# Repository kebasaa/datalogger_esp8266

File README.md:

# Asynchronous datalogger using ESP8266

Asynchronous datalogger using ESP8266 for logging scientific sensors to MicroSD

## Offline dashboard

The firmware starts a protected setup access point when it has no saved Wi-Fi
credentials and, after a 30-second station outage, exposes the dashboard again
through that access point. Change `HOTSPOT_PASSWORD`, `DASHBOARD_USER` and
`DASHBOARD_PASSWORD` in `src/main.cpp` before deployment.

Open `http://192.168.4.1/` on the access point, or the logger's address on your
network. The dashboard has four tabs:

- **Status** — whether the logger is actually recording, GPS fix and time
  quality, battery, free heap, MicroSD space and write errors, per-bus I2C
  health and the supervisor counters. Updates once a second.
- **Calibration** — sessions, live raw versus calibrated readings, zero/span
  and differential calibration, and the stored coefficients.
- **WiFi** — scan for networks and join one.
- **Console** — runs the same commands as the serial port, for when something
  needs poking at and no cable is to hand.

It is a small single-page app served from the logger's own flash: no internet
connection is needed and nothing is loaded from a CDN. It scales from a phone
in the field to a desktop browser, and follows your system's light or dark
theme (with a toggle to override).

> The web interface lives in `web/src/`. A pre-build script minifies and gzips
> it into `data/h4/`, so after changing it you must upload the filesystem as
> well as the firmware:
>
> ```bash
> pio run -e d1_mini_pro -t upload -t uploadfs
> ```

GPS is connected directly to the I2C bus. Its reader is deliberately separate
from the TCA9548A channels; do not pass the multiplexer to the GPS constructor
unless the hardware wiring changes.

Sensor & logger testing in the field

## Serial commands

The web interface has no private channel to the firmware: every button on it
runs one of the commands below, over `GET /rest/<command>/<parameters>`. So
anything the dashboard can do can also be done from the serial port or with
`curl`, which is what you want when no Wi-Fi is available, when calibrating
from a script, or when a logger needs rescuing.

### Connecting

Connect at **115200 baud** (`monitor_speed` in `platformio.ini`; the firmware
takes the same value through `PROJ_BAUD_RATE`):

```bash
pio device monitor -e d1_mini_pro
```

Type a command and press Enter. Parameters are separated by a forward slash,
with no spaces:

```
command/parameter/parameter/...
```

Commands are case-sensitive. `help` lists every command the firmware knows,
including the built-in H4 ones described at the end of this section.

### Overview

| Command | Parameters | Needs a session | What it does |
| --- | --- | --- | --- |
| `cal_start` | none | – | Starts a calibration session |
| `cal_stop` | none | yes | Saves everything measured in the session |
| `cal_discard` | none | yes | Throws the session away without saving |
| `cal` | 3–4 | yes | Measures the sensor and calibrates from the reading |
| `set` | 5 | yes | Stores a reference and a measured value entered by hand |
| `show_cal` | none | no | Prints all stored calibration values |
| `cal_reset` | none | no | Clears every stored coefficient (opens and closes its own session) |
| `cal_select` | 2–3 | no | Chooses which quantity and sensor the dashboard's live reading follows |

### Calibration sessions

Calibration values live in flash memory, which wears out if written to too
often. Rather than saving on every calibration, the firmware collects them in a
session and writes them once:

1. `cal_start` — begins recording. Values change in memory only.
2. Any number of `cal` and `set` commands.
3. `cal_stop` — writes everything to flash in a single operation and appends one
   row to `calibration_<date>.csv` on the SD card. The row needs a valid GPS
   date; without a fix the values are still saved to flash, but the log line is
   skipped and `Error: No GPS fix` is printed.

`cal_discard` ends the session and throws the collected values away, leaving
what was previously stored untouched. `cal` and `set` refuse to run outside a
session and answer `Can't do now`, so it is always clear when values reach
flash.

A session that is left open and untouched saves itself after the number of
minutes set by `CALIBRATION_TIMEOUT_MINUTES` in `src/main.cpp` (30 by default,
0 to disable), so a forgotten calibration is not lost. Values collected in an
open session are used immediately for the logged data and are visible to
`show_cal`, but a power cut before `cal_stop` loses them.

The session is shared with the dashboard, because they are the same thing: the
Calibration tab's buttons issue `cal_start`/`cal_stop`/`cal_discard`, so a
session begun over serial is visible in the browser and vice versa.

### Quantity names and units

The quantity is one of the names below. Which ones exist depends on the sensors
enabled in `src/main.cpp`:

| Name | Enabled by | Sensor measures | Reference for `cal/zero` | Reference for `cal/span` | Reference for `set` |
| --- | --- | --- | --- | --- | --- |
| `temperature` | `BME280_BUSES` | °C | °C | °C | °C |
| `pressure` | `BME280_BUSES` | Pa | Pa | Pa | Pa |
| `h2o` | `BME280_BUSES` | mmol/mol | mmol/mol | **dew point in °C** | mmol/mol |
| `co2` | `SCD30_BUSES` | ppm | ppm | ppm | ppm |
| `o2` | `SEN0465_BUSES` | % vol | % vol | % vol | % vol |

Water vapour is the one quantity whose reference is not always in the unit the
sensor reports, because the two calibration points are produced differently. A
span calibration uses a dew-point generator, so `cal/span/h2o/...` takes a **dew
point in °C** and converts it to a mole fraction using the measured air pressure.
A zero calibration uses dry gas, so `cal/zero/h2o/...` takes a mole fraction in
mmol/mol — `cal/zero/h2o/0` with no reference therefore calibrates against dry
air (0 mmol/mol), which is what flushing the sensor with a desiccant or zero air
gives you. `set` never converts anything, so it always expects mmol/mol.

The same split applies to the dashboard: for water vapour the "Zero gas" box is
in mmol/mol and the "Span gas" box is a dew point in °C.

Sensor numbers are **0-based**: with `BME280_BUSES 0, 1` the two sensors are
`0` and `1`. For `cal/zero` and `cal/span`, a sensor number that does not exist
is skipped rather than stored.

### `cal` — measure and calibrate

Takes a reading from the sensor itself and stores it against a known reference.
It averages 10 readings taken about one second apart, so it takes roughly ten
seconds; the command returns immediately and the result appears afterwards.

```
cal/zero/<quantity>/<sensor>
cal/zero/<quantity>/<sensor>/<reference>
cal/span/<quantity>/<sensor>/<reference>
cal/diff/<quantity>/low
cal/diff/<quantity>/high
```

`zero` without a reference uses 0.0. `span` always needs one.

```
cal/zero/co2/1              zero-calibrate CO2 sensor 1 against 0 ppm
cal/zero/co2/1/0.54         zero-calibrate CO2 sensor 1 against 0.54 ppm
cal/span/co2/1/409.87       span-calibrate CO2 sensor 1 against 409.87 ppm
cal/zero/h2o/0              zero-calibrate H2O sensor 0 against dry air (0 mmol/mol)
cal/zero/h2o/0/0.05         zero-calibrate H2O sensor 0 against 0.05 mmol/mol
cal/span/h2o/0/1.31         span-calibrate H2O sensor 0 against a 1.31 °C dew point
cal/span/temperature/0/20.5 span-calibrate temperature sensor 0 against 20.5 °C
cal/diff/co2/low            measure both CO2 sensors at the low concentration
cal/diff/co2/high           measure both CO2 sensors at the high concentration
```

Timing rules the firmware enforces:

- A `span` calibration must follow its `zero` by at least 10 seconds and no more
  than 2 hours, otherwise it is rejected and the reason is printed. Temperature
  is exempt from the 2-hour limit.
- `cal/diff/<quantity>/high` must follow the matching `low` by 10 to 600
  seconds. After 600 seconds only a simple offset is applied instead of a full
  linear correction, and the firmware says so.
- `cal/diff` measures sensors 0 and 1 together and so needs two sensors of that
  type. It takes no sensor number.
- Only one calibration runs at a time; a second one while the first is still
  measuring is ignored.

### `set` — enter values by hand

Stores a reference value and the corresponding sensor reading without measuring
anything. Useful for entering figures from a calibration certificate or from an
earlier session. Requires exactly five parameters.

```
set/<zero|span>/<quantity>/<sensor>/<reference>/<measured>
```

```
set/zero/co2/1/12.07/13.08      sensor 1 read 13.08 ppm when the true value was 12.07
set/span/co2/1/376.87/402.87    sensor 1 read 402.87 ppm when the true value was 376.87
```

Unlike `cal`, `set` ignores the timing rules above, so a `span` can be entered
without a preceding `zero`.

### `show_cal`

Prints every stored calibration value, including values collected in a session
that has not been saved yet. Works with or without a session.

```
show_cal
```

```
Calibration coefficients:
  - sen_co2_0_zero: 13.08
  - sen_co2_0_span: 402.87
  - sen_co2_0_diff: nan
  ...
```

The names read `<sen|ref>_<quantity>_<sensor>_<type>`, where `ref_` is the known
reference value and `sen_` is what the sensor read. For the `diff` type, `ref_`
holds the low value and `sen_` the high one. `nan` means not calibrated.

### `cal_reset`

Clears every stored calibration coefficient, for every quantity and sensor.
This is the "Reset all" button on the Calibration tab. It does not need a
session: if none is open it opens and closes one itself, so the whole reset
costs a single write to flash.

```
cal_reset
```

### `cal_select`

Chooses which quantity and sensor the dashboard's live reading follows. It
changes nothing that gets logged and no calibration depends on it — `cal` and
`set` always take their quantity and sensor as explicit parameters.

```
cal_select/<quantity>/<sensor>[/<differential quantity>]
```

```
cal_select/co2/1
cal_select/co2/1/h2o
```

Until a selection is made the logger does not read a sensor for the dashboard
at all, which keeps the web interface off the I2C bus unless someone is
actually watching a value.

### Worked examples

A full zero and span calibration of one CO<sub>2</sub> sensor, saved in a single
write to flash:

```
cal_start
cal/zero/co2/1                 (flush with zero gas, wait ~10 s for the reading)
cal/span/co2/1/409.87          (flush with 409.87 ppm span gas, at least 10 s later)
show_cal                       (check the values before committing to them)
cal_stop
```

A differential calibration comparing two sensors, where the second run went
wrong and is thrown away:

```
cal_start
cal/diff/co2/low               (both sensors at the low concentration)
cal/diff/co2/high              (both sensors at the high concentration, 10-600 s later)
cal_discard                    (nothing is written; the old values remain)
```

Entering values from a certificate for both sensors:

```
cal_start
set/zero/co2/0/0.0/1.42
set/span/co2/0/400.0/398.15
set/zero/co2/1/0.0/2.07
set/span/co2/1/400.0/403.44
cal_stop
```

### Replies

A command that succeeds prints its own progress messages and nothing else. A
command that fails prints one of these, in addition to a line explaining what
was wrong:

| Reply | Meaning |
| --- | --- |
| `Unknown cmd` | No such command |
| `Too few parameters` | Not enough parameters |
| `Too many parameters` | Too many parameters |
| `Numeric value expected` | A sensor number or reference value was not a number |
| `Incorrect Payload Format` | An unknown quantity, calibration type, or something other than `low`/`high` |
| `Can't do now` | No session open, or a session is already open |

Calibrations rejected by the timing rules are reported as plain text, for
example `<10s since zero calibration. Are you sure the span gas is stable?`.

### Built-in commands

H4, the framework underneath, adds its own commands. Run `help` for the full
list, which depends on how the framework is configured — the reporting commands
(`h4/show/...`) are compiled out in this build, because `H4P_LOG_MESSAGES` is 0.
The ones worth knowing:

| Command | What it does |
| --- | --- |
| `help` | Lists every available command |
| `h4/reboot` | Restarts the logger |
| `h4/clear` | Erases all stored settings, **including every calibration** |
| `h4/factory` | Factory reset; also erases every calibration |

Both `h4/clear` and `h4/factory` delete the file the calibrations live in. Save
anything you need first — `show_cal` prints the values, and every `cal_stop`
appends them to `calibration_<date>.csv` on the SD card.

`h4/factory` is also the way back into access-point mode: it clears the stored
Wi-Fi credentials, so the logger starts its own hotspot on the next boot.
Follow it with `h4/reboot`.

### Over HTTP

Every command above is also reachable at `GET /rest/<command>/<parameters>`,
protected by the same login as the dashboard:

```bash
curl -u admin:datalogger http://<logger-address>/rest/show_cal
curl -u admin:datalogger http://<logger-address>/rest/cal/zero/co2/1
```

The reply is JSON — `res` is 0 on success, and `lines` holds what the command
printed:

```json
{"res":0,"msg":"OK","lines":["Calibration coefficients:","  - sen_co2_0_zero: 13.08"]}
```

Alongside the commands there are a few read-only endpoints the dashboard uses,
which are also handy for scripted monitoring:

| Endpoint | What it returns |
| --- | --- |
| `GET /api/status` | One JSON snapshot of everything on the Status tab |
| `GET /api/events` | The same payload once a second, as a server-sent event stream |
| `GET /api/cal` | Stored calibration coefficients, as JSON |
| `GET /api/wifi/scan` | Networks the logger can see (access-point mode only) |

## Prerequisites
- Requires a GPS module for date, time and location

The following sensors/components are implemented currently:
- [Texas Instruments ADS1115](https://www.ti.com/product/ADS1115) analogue multiplexer
- [Texas Instruments TCA9548](https://www.ti.com/product/TCA9548A) i<sup>2</sup>c multiplexer
- MicroSD card data storage with circular storage buffer
- Analogue battery charge reading (voltage)
- Environmental physics equations
- [Sierra Wireless XA1110](https://source.sierrawireless.com/devices/positioning-modules/xa1110/) GPS module
- [Sensirion SCD-30](https://sensirion.com/products/catalog/SCD30) CO<sub>2</sub> sensor
- [DFRobot SEN0465](https://www.dfrobot.com/product-2510.html) O<sub>2</sub> sensor
- [Bosch BME280](https://www.bosch-sensortec.com/products/environmental-sensors/humidity-sensors-bme280/) air temperature, relative humidity & pressure sensor
- [Melexis MLX90614](https://www.melexis.com/en/product/MLX90614/Digital-Plug-Play-Infrared-Thermometer-TO-Can) thermal radiation sensor
- WIFI & web interface
- Zero, span and differential calibration of every measured quantity, controlled
  from the web interface or the serial port (see [Serial commands](#serial-commands)),
  collected into sessions so a calibration is written to flash only once

To be done:
- Single-bus operation (`I2C_MULTI 0` in `src/config.h`) does not currently
  compile; only the multiplexed dual-bus configuration builds
- When the dashboard pre-fills the "Span gas" box for water vapour it shows the
  stored mole fraction, although the box expects a dew point. Displaying it as a
  dew point needs a mole-fraction-to-dew-point conversion, which
  `lib/Environmental` does not have yet
- Guard the differential-to-absolute conversion against division by zero when
  the two differential calibration points are nearly equal
- The differential check that rejects a high calibration point too close to the
  low one uses a fixed threshold of 100, regardless of the unit of the quantity
  being calibrated
- Cache the calibration coefficients instead of re-reading twelve stored values
  on every conversion, once per second per quantity

## How to Cite

This citation does not work yet. Simply cite the github repository as a website for now:
Muller (2025). *datalogger_esp8266: Asynchronous datalogger using ESP8266*

## License

This software is distributed under the GNU GPL version 3. Any modification of the code in this repository may only be released under the same license, and with attribution of authorship of the original code (i.e., citation above).

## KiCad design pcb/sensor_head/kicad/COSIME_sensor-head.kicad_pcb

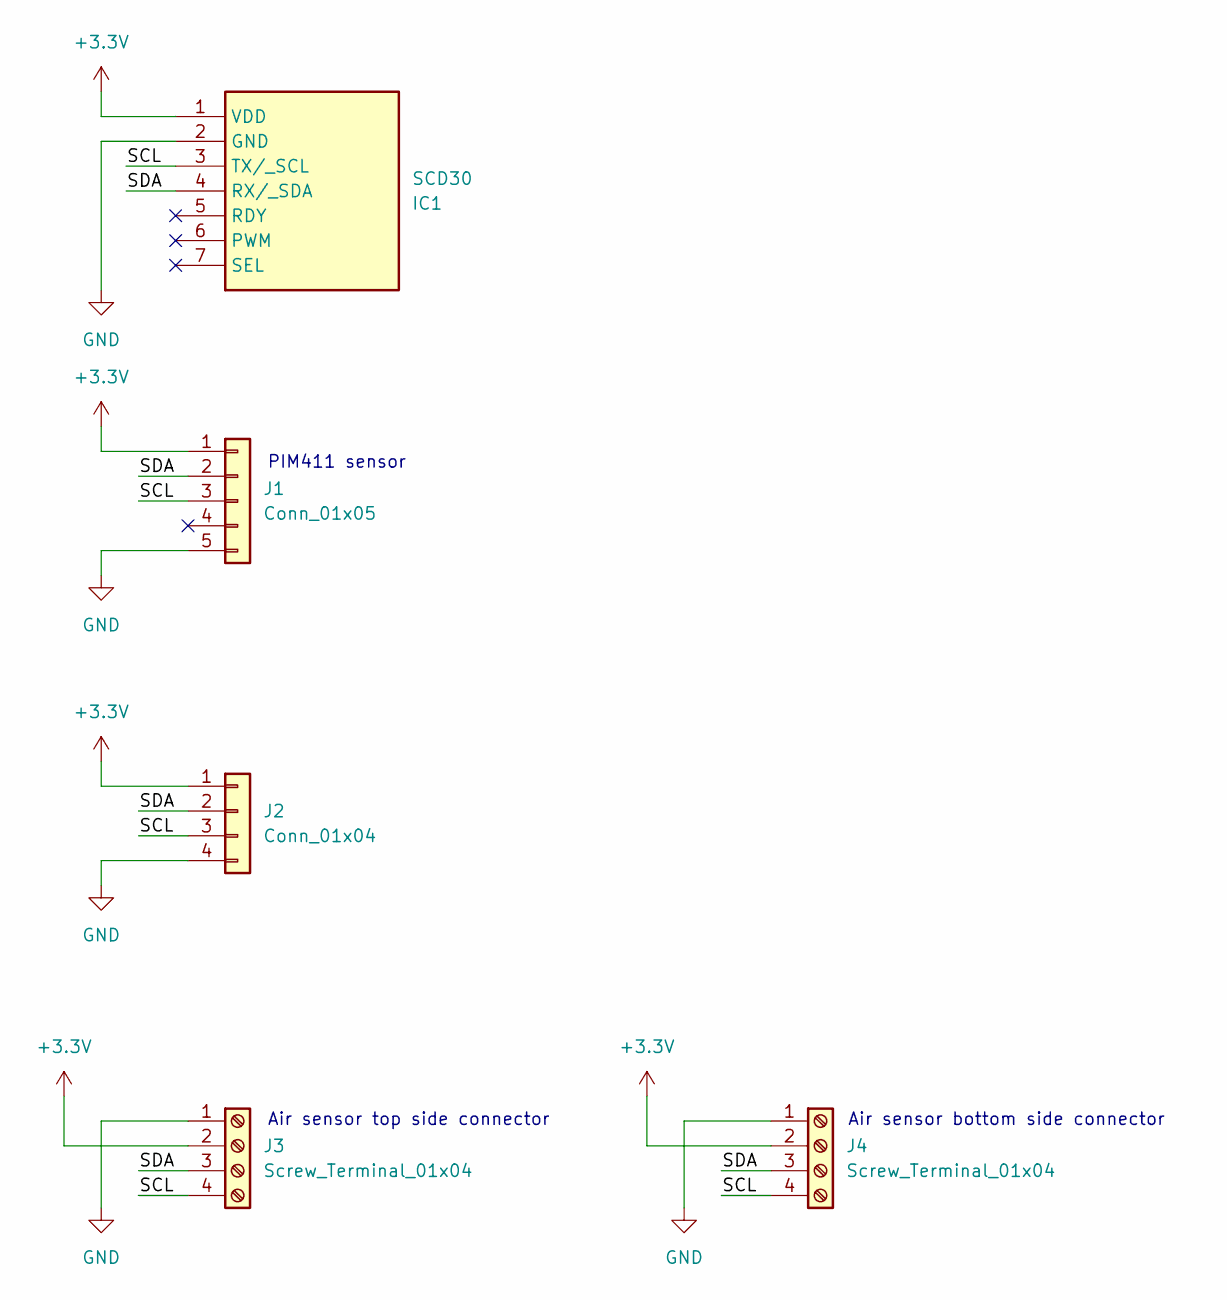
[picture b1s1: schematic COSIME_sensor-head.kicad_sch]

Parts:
IC1: SCD30; Manufacturer_Part_Number SCD30; Mouser Part Number 403-SCD30
J1: Conn_01x05; PinSocket_1x05_P2.54mm_Vertical
J2: Conn_01x04; PinSocket_1x04_P2.54mm_Vertical
J3, J4: Screw_Terminal_01x04; 1778719

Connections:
+3.3V: IC1.1 (VDD), J1.1, J2.1, J3.2, J4.2
/SCL: IC1.3 (TX/_SCL), J1.3, J2.3, J3.4, J4.4
/SDA: IC1.4 (RX/_SDA), J1.2, J2.2, J3.3, J4.3
GND: IC1.2 (GND), J1.5, J2.4, J3.1, J4.1

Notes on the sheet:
Air sensor top side connector
Air sensor bottom side connector
PIM411 sensor

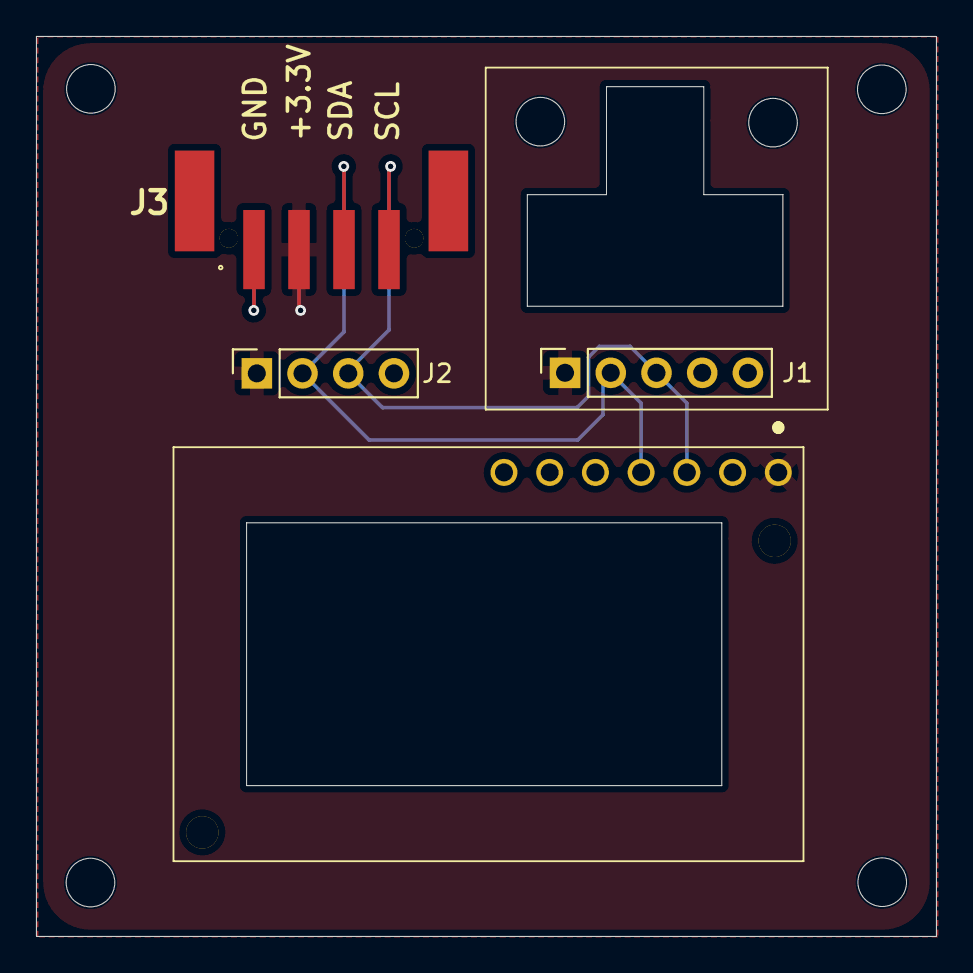
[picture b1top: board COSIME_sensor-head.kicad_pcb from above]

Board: 2 copper layers, 50.0 x 50.0 mm, 5 parts (1 on the bottom side), 4 nets.

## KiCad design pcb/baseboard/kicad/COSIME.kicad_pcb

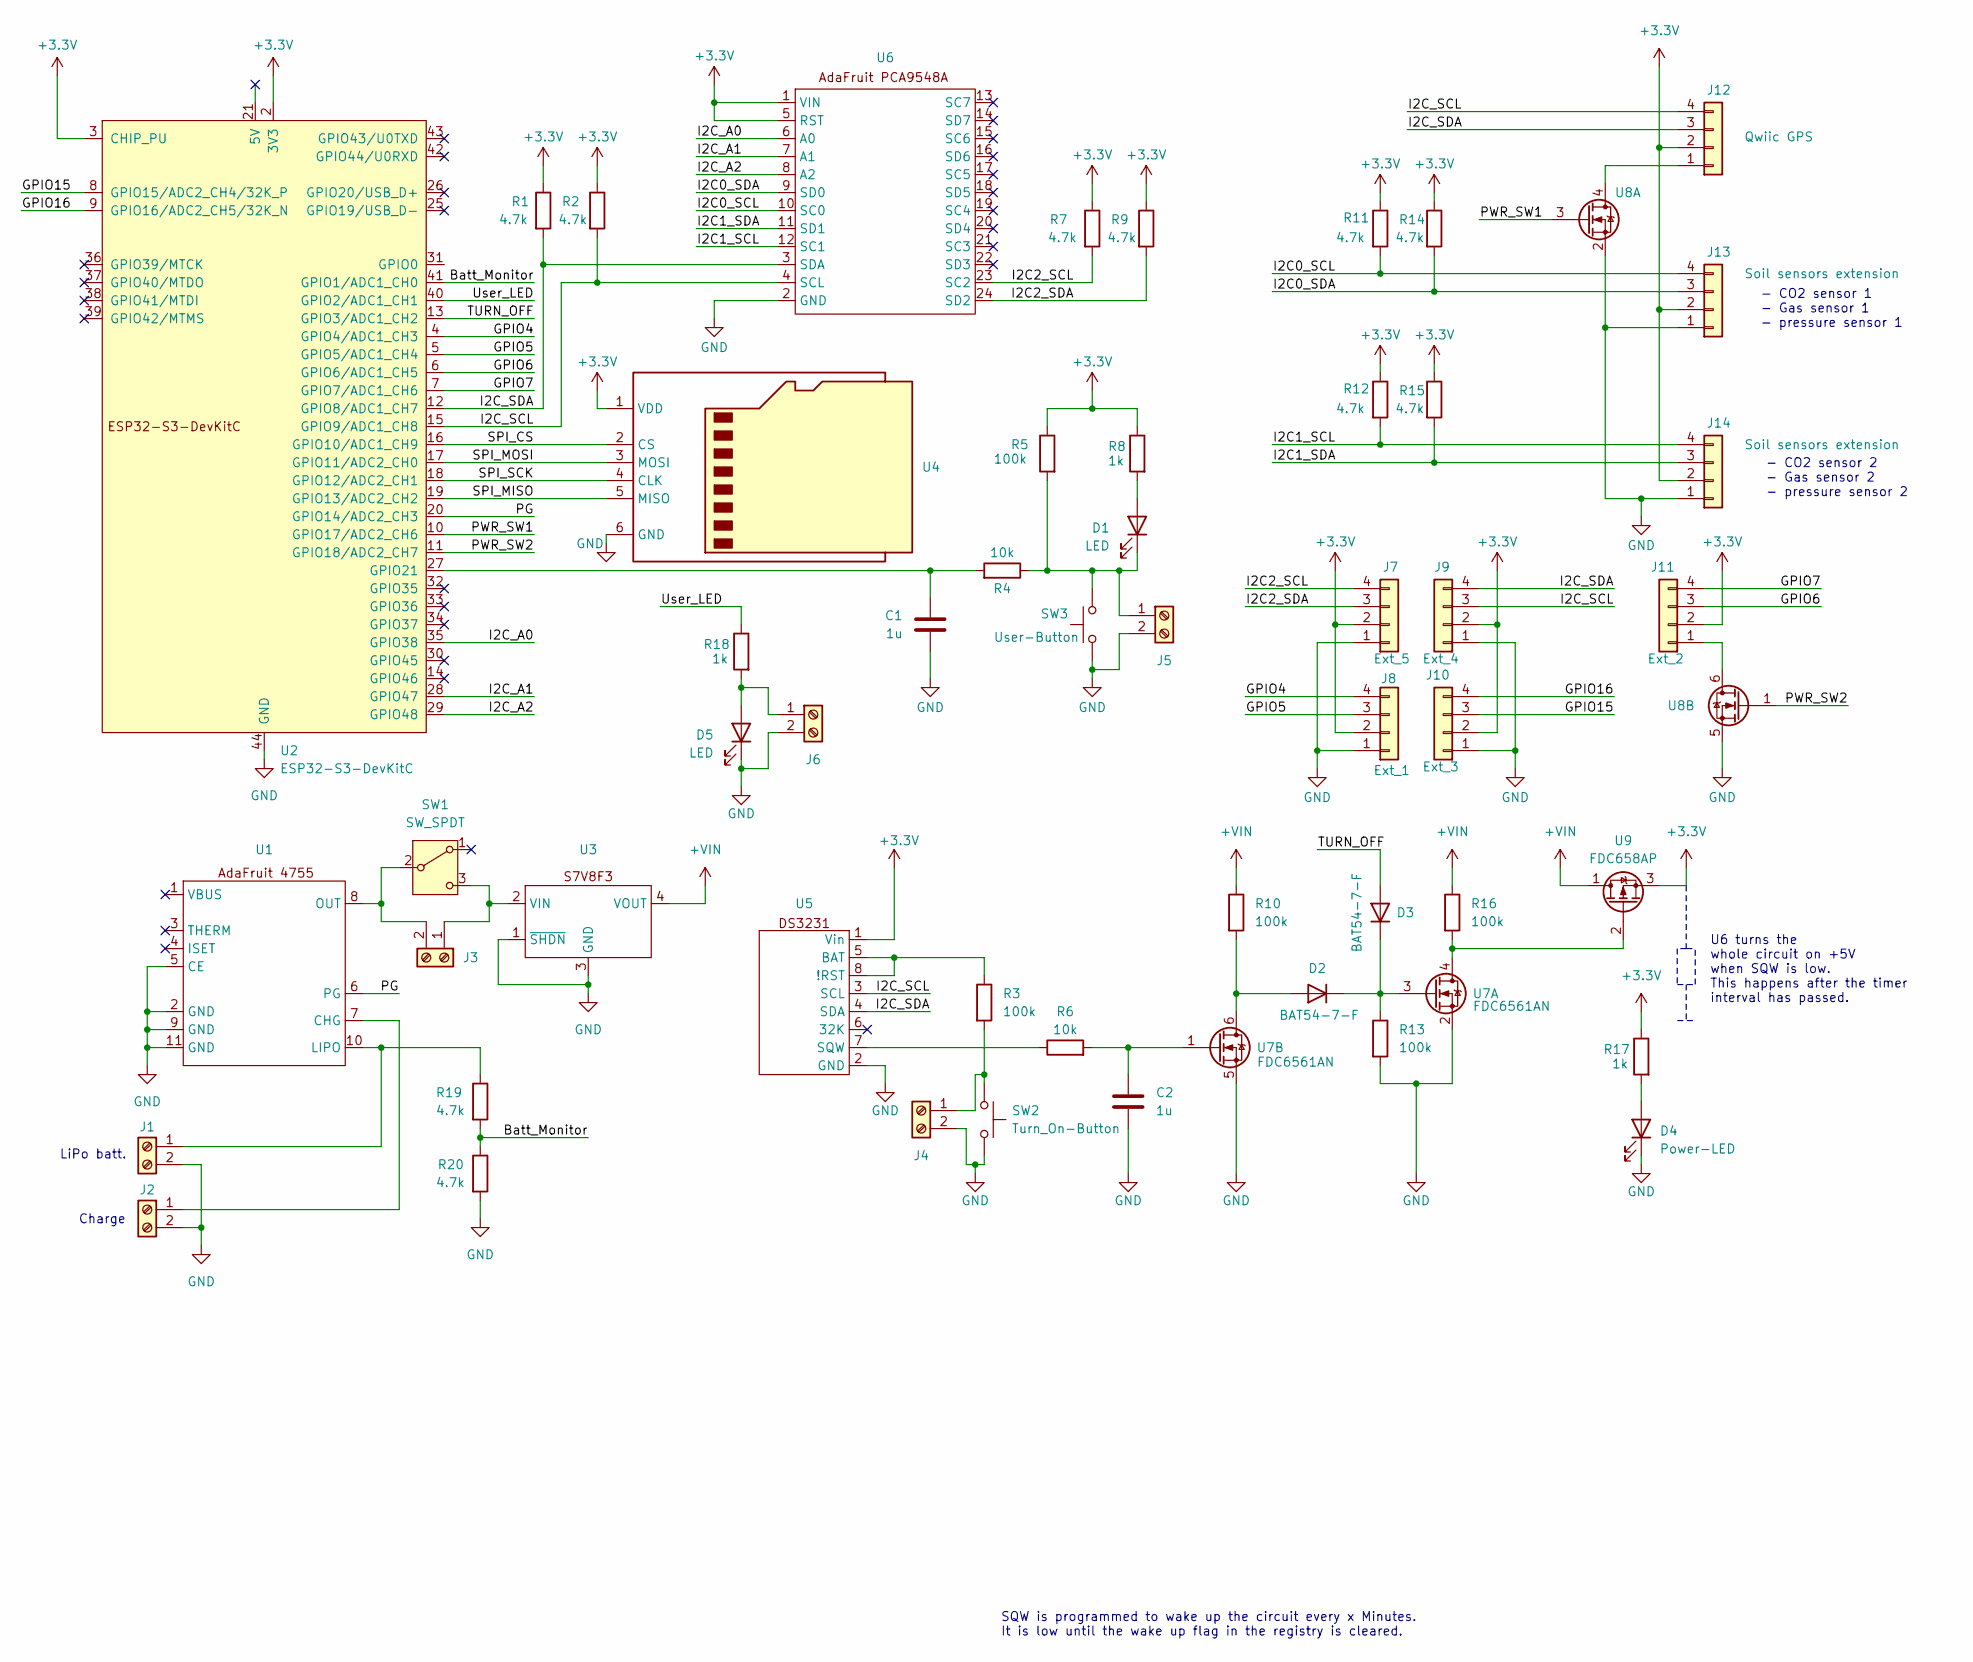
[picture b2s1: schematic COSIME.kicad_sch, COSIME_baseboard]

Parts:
C1, C2: 1u; C_0603_1608Metric_Pad1.08x0.95mm_HandSolder
D1, D5: LED; LED_0805_2012Metric_Pad1.15x1.40mm_HandSolder
D2, D3: BAT54-7-F; D_DO-35_SOD27_P7.62mm_Horizontal
D4: Power-LED; LED_0805_2012Metric_Pad1.15x1.40mm_HandSolder
J1, J2, J3, J4, J5, J6: Screw_Terminal_01x02; 1839198
J7: Ext_5; 1778719
J8: Ext_1; 1778719
J9: Ext_4; 1778719
J10: Ext_3; 1778719
J11: Ext_2; 1778719
J12: Qwiic GPS; 1778719
J13, J14: Soil sensors extension; 1778719
R1, R2, R7, R9, R11, R12, R14, R15, R19, R20: 4.7k; R_0603_1608Metric_Pad0.98x0.95mm_HandSolder
R3, R5, R10, R13, R16: 100k; R_0603_1608Metric_Pad0.98x0.95mm_HandSolder
R4, R6: 10k; R_0603_1608Metric_Pad0.98x0.95mm_HandSolder
R8, R17, R18: 1k; R_0603_1608Metric_Pad0.98x0.95mm_HandSolder
SW1: SW_SPDT; 500SSP1S2M2QEA
SW2: Turn_On-Button; SW_SPST_TL3305A
SW3: User-Button; SW_SPST_TL3305A
U1: 4755
U2: ESP32-S3-DevKitC
U3: Pololu_S7V8X
U4: MSD_BO1_SD-Card_Reader
U5: DS3231_Adafruit
U6: TCA9548A_AdaFruit
U7: FDC6561AN; SOT95P280X110-6N
U8: SOT95P280X110-6N
U9: FDC658AP; SOT95P275X110-6N_FDC658AP; Manufacturer_Part_Number FDC658AP; Mouser Part Number 512-FDC658AP

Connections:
+3.3V: J7.2, J8.2, J9.2, J10.2, J11.2, J12.2, J13.2, J14.2, R1.1, R2.1, R5.1, R7.1, R8.1, R9.1, R11.1, R12.1, R14.1, R15.1, R17.1, U2.1 (3V3), U2.2 (3V3), U2.3 (CHIP_PU), U4.1 (VDD), U5.1 (Vin), U6.1 (VIN), U6.5 (RST), U9.3
+VIN: R10.1, R16.1, U3.4 (VOUT), U9.1
/<NO NET>: J9.3, J12.4, R2.2, U2.15 (GPIO9/ADC1_CH8), U5.3 (SCL), U6.4 (SCL)
/Batt_Monitor: R19.2, R20.1, U2.41 (GPIO1/ADC1_CH0)
/GPIO4: J8.4, U2.4 (GPIO4/ADC1_CH3)
/GPIO5: J8.3, U2.5 (GPIO5/ADC1_CH4)
/GPIO6: J11.3, U2.6 (GPIO6/ADC1_CH5)
/GPIO7: J11.4, U2.7 (GPIO7/ADC1_CH6)
/GPIO15: J10.3, U2.8 (GPIO15/ADC2_CH4/32K_P)
/GPIO16: J10.4, U2.9 (GPIO16/ADC2_CH5/32K_N)
/I2C0_SCL: J13.4, R11.2, U6.10 (SC0)
/I2C0_SDA: J13.3, R14.2, U6.9 (SD0)
/I2C1_SCL: J14.4, R12.2, U6.12 (SC1)
/I2C1_SDA: J14.3, R15.2, U6.11 (SD1)
/I2C2_SCL: J7.4, R7.2, U6.23 (SC2)
/I2C2_SDA: J7.3, R9.2, U6.24 (SD2)
/I2C_A0: U2.35 (GPIO38), U6.6 (A0)
/I2C_A1: U2.28 (GPIO47), U6.7 (A1)
/I2C_A2: U2.29 (GPIO48), U6.8 (A2)
/I2C_SDA: J9.4, J12.3, R1.2, U2.12 (GPIO8/ADC1_CH7), U5.4 (SDA), U6.3 (SDA)
/PG: U1.6 (PG), U2.20 (GPIO14/ADC2_CH3)
/PWR_SW1: U2.10 (GPIO17/ADC2_CH6), U8.3
/PWR_SW2: U2.11 (GPIO18/ADC2_CH7), U8.1
/SPI_CS: U2.16 (GPIO10/ADC1_CH9), U4.2 (CS)
/SPI_MISO: U2.19 (GPIO13/ADC2_CH2), U4.5 (MISO)
/SPI_MOSI: U2.17 (GPIO11/ADC2_CH0), U4.3 (MOSI)
/SPI_SCK: U2.18 (GPIO12/ADC2_CH1), U4.4 (CLK)
/TURN_OFF: D3.2 (A), U2.13 (GPIO3/ADC1_CH2)
/User_LED: R18.1, U2.40 (GPIO2/ADC1_CH1)
GND: C1.2, C2.2, D4.1 (K), D5.1 (K), J1.2, J2.2, J4.2, J5.2, J6.2, J7.1, J8.1, J9.1, J10.1, J13.1, J14.1, R13.2, R20.2, SW2.2, SW3.2, U1.2 (GND), U1.5 (CE), U1.9 (GND), U1.11 (GND), U2.22 (GND), U2.23 (GND), U2.24 (GND), U2.44 (GND), U3.1 (~SHDN), U3.3 (GND), U4.6 (GND), U5.2 (GND), U6.2 (GND), U7.2, U7.5, U8.2, U8.5
unnamed: C2.1, R6.2, U7.1
unnamed: D1.2 (A), R8.2
unnamed: D1.1 (K), J5.1, R4.1, R5.2, SW3.1
unnamed: D2.2 (A), R10.2, U7.6
unnamed: D2.1 (K), D3.1 (K), R13.1, U7.3
unnamed: D4.2 (A), R17.2
unnamed: D5.2 (A), J6.1, R18.2
unnamed: J1.1, R19.1, U1.10 (LIPO)
unnamed: J2.1, U1.7 (CHG)
unnamed: J3.1, SW1.3 (C), U3.2 (VIN)
unnamed: J3.2, SW1.2 (B), U1.8 (OUT)
unnamed: J4.1, R3.2, SW2.1
unnamed: J11.1, U8.6
unnamed: J12.1, U8.4
unnamed: R16.2, U7.4, U9.2
unnamed: C1.1, R4.2, U2.27 (GPIO21)
unnamed: R3.1, U5.5 (BAT), U5.8 (!RST)
unnamed: R6.1, U5.7 (SQW)

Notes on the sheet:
U6 turns the whole circuit on +5V when SQW is low. This happens after the timer interval has passed.
SQW is programmed to wake up the circuit every x Minutes. It is low until the wake up flag in the registry is cleared.
LiPo batt.
Charge
- CO2 sensor 1 - Gas sensor 1 - pressure sensor 1
- CO2 sensor 2 - Gas sensor 2 - pressure sensor 2

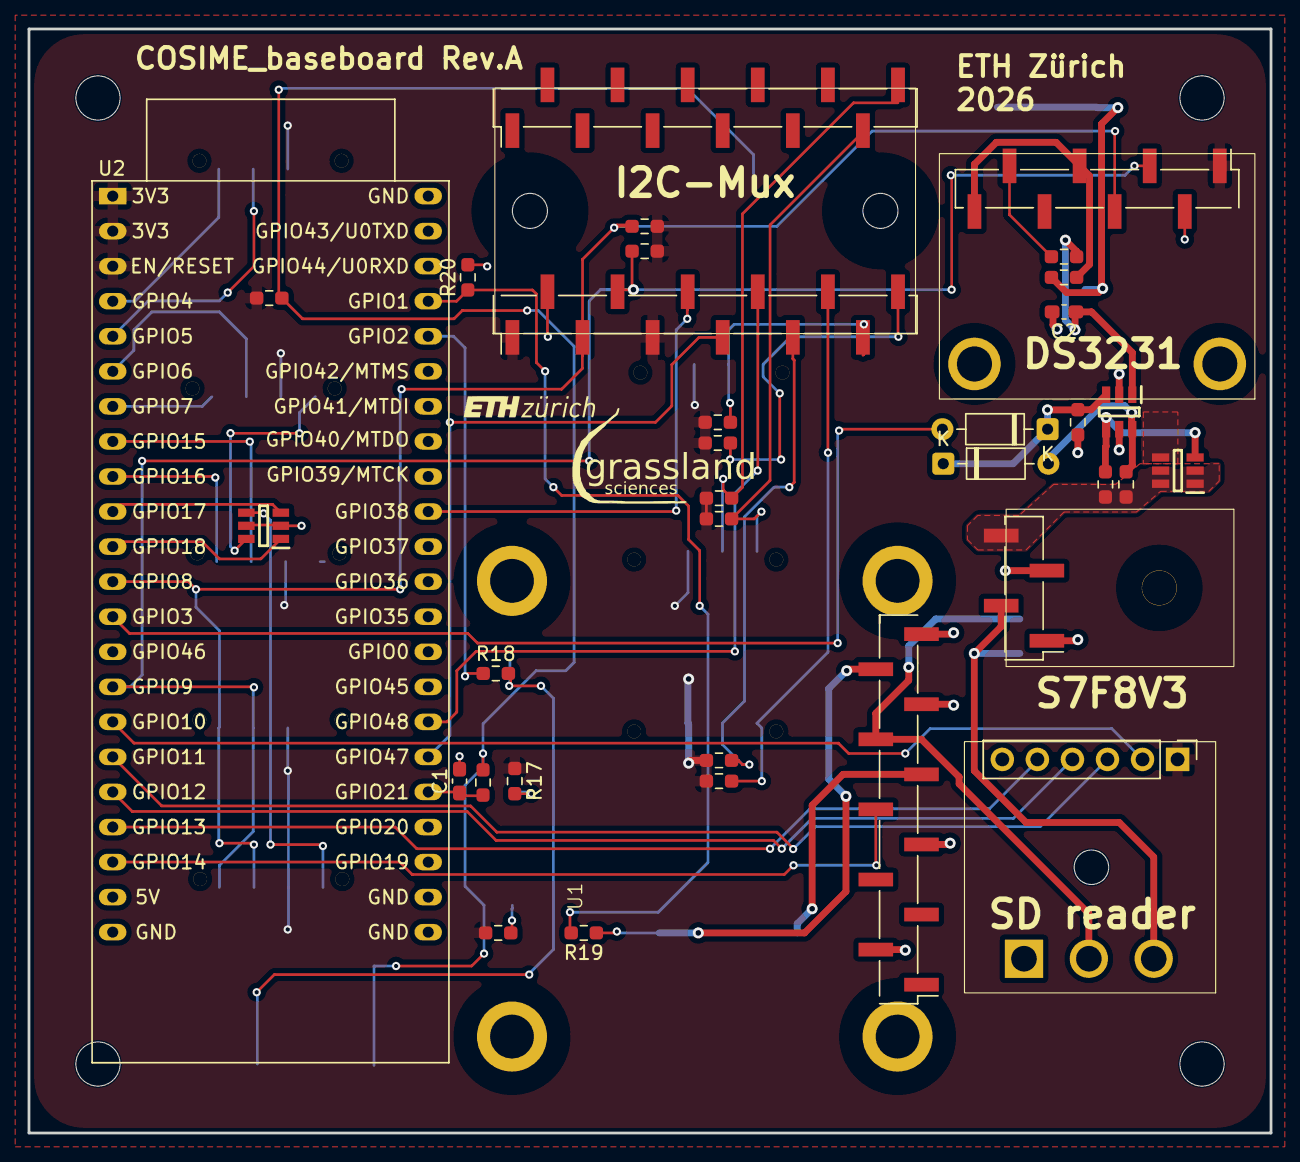
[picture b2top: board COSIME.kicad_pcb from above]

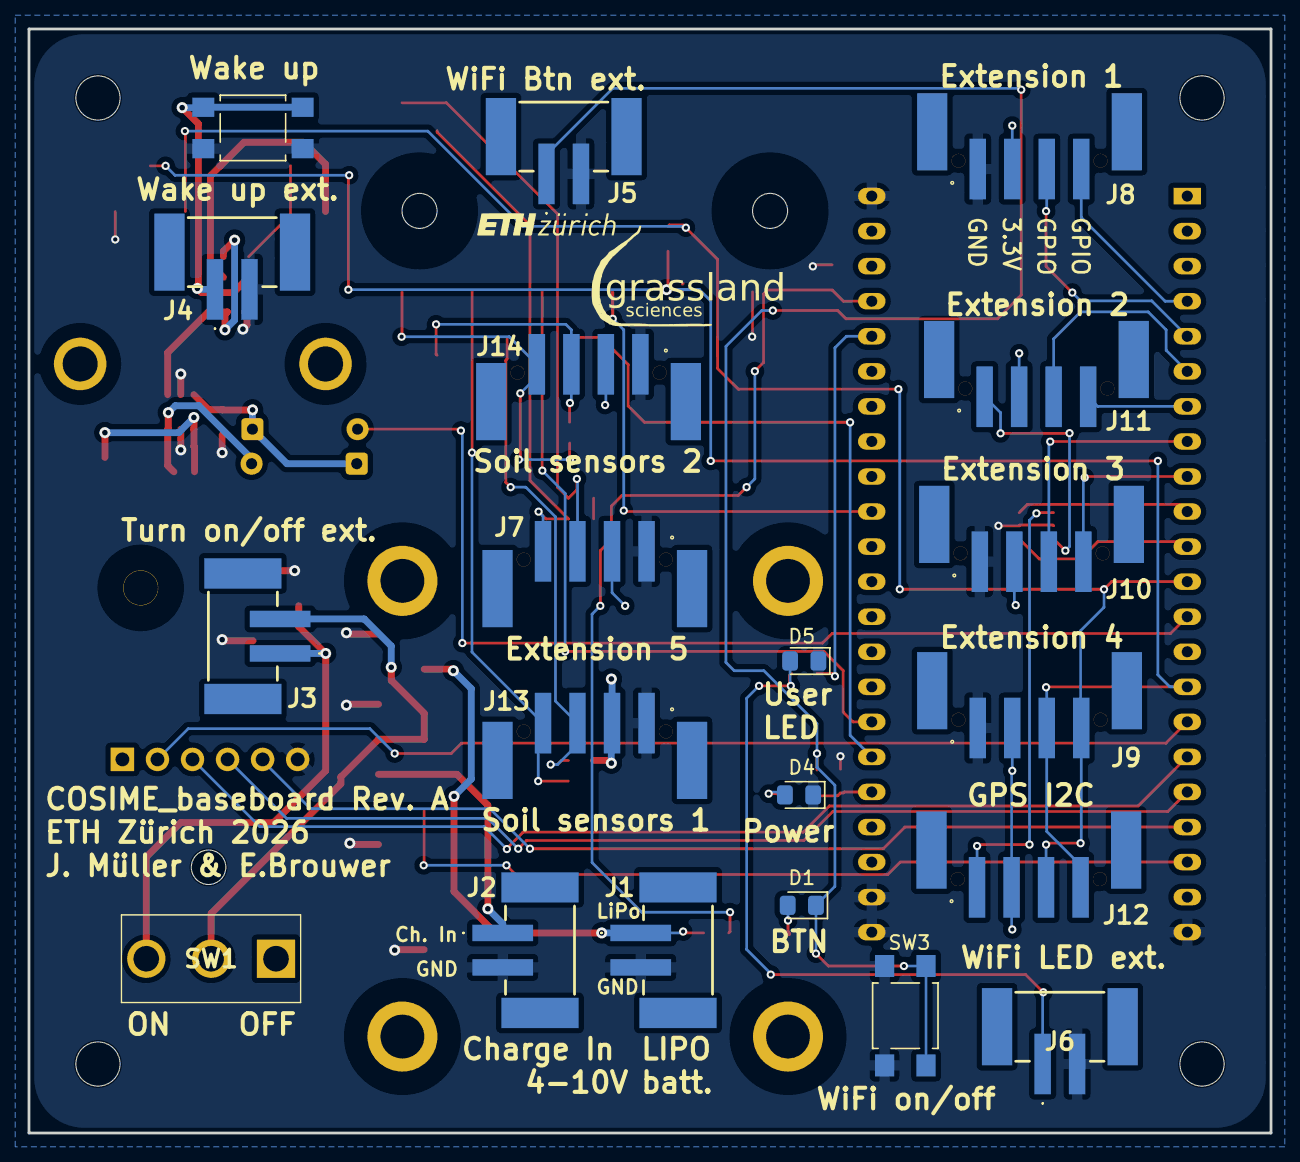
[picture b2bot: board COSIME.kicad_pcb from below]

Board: 2 copper layers, 90.0 x 80.0 mm, 53 parts (20 on the bottom side), 48 nets.

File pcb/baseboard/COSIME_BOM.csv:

Reference;Qty;Qty for 3;Value;stock;Footprint;Datasheet
C1,C2;2;6;1u;M;603;
D1,D5;2;6;LED;M;LED_SMD:LED_0805_2012Metric_Pad1.15x1.40mm_HandSolder;
D2,D3;2;6;BAT54-7-F;M;Diode_THT:D_DO-35_SOD27_P7.62mm_Horizontal;http://www.vishay.com/docs/85622/1n914.pdf
D4;1;3;Power-LED;M;LED_SMD:LED_0805_2012Metric_Pad1.15x1.40mm_HandSolder;
J1,J2,J3,J4,J5,J6;6;18;Screw_Terminal_01x02;M;SamacSys_Parts1:1839198;
J7;1;3;Ext_5;M;SamacSys_Parts1:1778719;
J8;1;3;Ext_1;M;SamacSys_Parts1:1778719;
J9;1;3;Ext_4;M;SamacSys_Parts1:1778719;
J10;1;3;Ext_3;M;SamacSys_Parts1:1778719;
J11;1;3;Ext_2;M;SamacSys_Parts1:1778719;
J12;1;3;Qwiic GPS;M;SamacSys_Parts1:1778719;
J13,J14;2;6;Soil sensors extension;M;SamacSys_Parts1:1778719;
R1,R2,R7,R9,R11,R12,R14,R15;8;24;4.7k;no;Resistor_SMD:R_0603_1608Metric_Pad0.98x0.95mm_HandSolder;
R3,R5,R10,R13,R16;5;15;100k;M;Resistor_SMD:R_0603_1608Metric_Pad0.98x0.95mm_HandSolder;
R4,R6;2;6;10k;M;Resistor_SMD:R_0603_1608Metric_Pad0.98x0.95mm_HandSolder;
R8,R17,R18;3;9;1k;M;Resistor_SMD:R_0603_1608Metric_Pad0.98x0.95mm_HandSolder;
SW1;1;3;SW_SPDT;M;SamacSys_Parts1:500SSP1S2M2QEA;
SW2;1;3;Turn_On-Button;M;Button_Switch_SMD:SW_SPST_TL3305A;
SW3;1;3;User-Button;M;Button_Switch_SMD:SW_SPST_TL3305A;
U1;1;3;;M;SamacSys_Parts1:4755;https://www.digikey.ch/de/products/detail/adafruit-industrie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
U2;1;3;ESP32-S3-DevKitC;M;PCM_Espressif:ESP32-S3-DevKitC;https://www.mouser.ch/de/ProductDetail/Espressif-Systems/ESP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
U3;1;3;;Eck;SamacSys_Parts1:Pololu_S7V8X;https://eckstein-shop.de/Pololu33VStep-UpStep-DownSpannungsr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
U4;1;3;;BB;SamacSys_Parts1:MSD_BO1_SD-Card_Reader;https://www.berrybase.de/en/micro-sd-card-reader-modul-mit-s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
U5;1;3;;M;SamacSys_Parts1:DS3231_Adafruit;https://www.bastelgarage.ch/rtc-ds3231-zeitmodul-mit-at24c32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
U6;1;3;;M;SamacSys_Parts1:TCA9548A_AdaFruit;https://www.bastelgarage.ch/8-kanal-i2c-multiplexer-tca9548asu
U7, U8;2;6;FDC6561AN;M;SamacSys_Parts1:SOT95P280X110-6N;
U9;1;3;FDC658AP;M;SamacSys_Parts1:SOT95P275X110-6N_FDC658AP;https://www.onsemi.com/pub/Collateral/FDC658AP-D.PDF
;2;6;PIM411 ;M;;https://www.mouser.ch/de/ProductDetail/Pimoroni/PIM411?qs=vL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
;2;6;SCD30;M;;
;1;3;CR1220;no;3V battery;

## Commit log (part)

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2025-06-19 Updated code & Readme
2025-06-28 Work on physics and sensors
    - Added environmental library (physics)
    - Remove SO-411 (non-functional)
    - Add testing routine for various tests
    - Minor changes to SD card, MLX90614 & GPS
    - Minor changes to BME280
2025-06-28 Remove obsolete stuff
2025-06-28 Minor changes
2025-06-28 Support for multiple i2c buses
2025-07-02 Implement O2 sensor
2025-07-02 Add O2 sensor and reorganise
2025-07-02 Update README & platformio requirements
2025-07-02 Add all sensors on both buses
2025-07-02 Rename battery library
2025-07-30 Update web/mobile interface
2025-08-27 Update buttons
2025-09-03 Smaller img for faster loading
2025-09-04 Update comment
2025-09-04 Minor fixes
2025-09-04 Add preliminary calibration logic
2025-09-08 Added calibration logic
2025-09-08 Update calibration logic
2025-09-23 Major UI changes & checksums
2025-09-23 Minor updates
2025-10-03 Multiplexer compatibility
2025-10-03 Organise settings
2025-10-03 Fix error in equation
2025-10-03 Improved calibration functionality
2025-10-03 Multiplexer, new buttons, calibration, etc
    Implement all changes from other sub-libraries
2025-10-17 Asynchronous calibration loop
    This is a major rewrite of the code base
2025-11-20 Test
2025-11-20 Switch BME280 lib & fix O2 units
2025-11-21 Added Utility functions
2025-11-21 Integrated utility functions
2025-11-21 Prep for Wifi AP
2025-11-21 Added calibration via Serial port
2025-11-21 Remove obsolete files
2025-11-24 Functionality for dewpoint and manual coeff setting
2025-11-24 Add command to show all cal. coefficients
2025-11-24 Show all calibrations logic
2025-11-24 Bugfixes
2026-01-27 Minor update
2026-02-13 Massive calibration update
2026-02-13 Integrate calibration logic
2026-05-29 Add image from prototype testing
2026-05-29 Update image
2026-06-03 Add preliminary data
2026-06-03 Analysis of test data
2026-06-03 Add diagnostics columns
2026-06-11 Added new data
2026-06-11 Update with fixes
2026-06-11 Fix timestamps
2026-06-11 Update test scripts
2026-06-18 New data
2026-06-18 Fix GPS bug
2026-06-18 Fix multiplexer reporting
2026-06-29 Improve analysis notebooks

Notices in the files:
README.md:
License:
This software is distributed under the GNU GPL version 3. Any modification of the code in this repository may only be released under the same license, and with attribution of authorship of the original code (i.e., citation above).
License: GPL v3
This citation does not work yet. Simply cite the github repository as a website for now:
